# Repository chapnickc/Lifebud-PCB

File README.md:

# Lifebud-PCB

This project contains the schematic 
and board files for the Lifebud project.

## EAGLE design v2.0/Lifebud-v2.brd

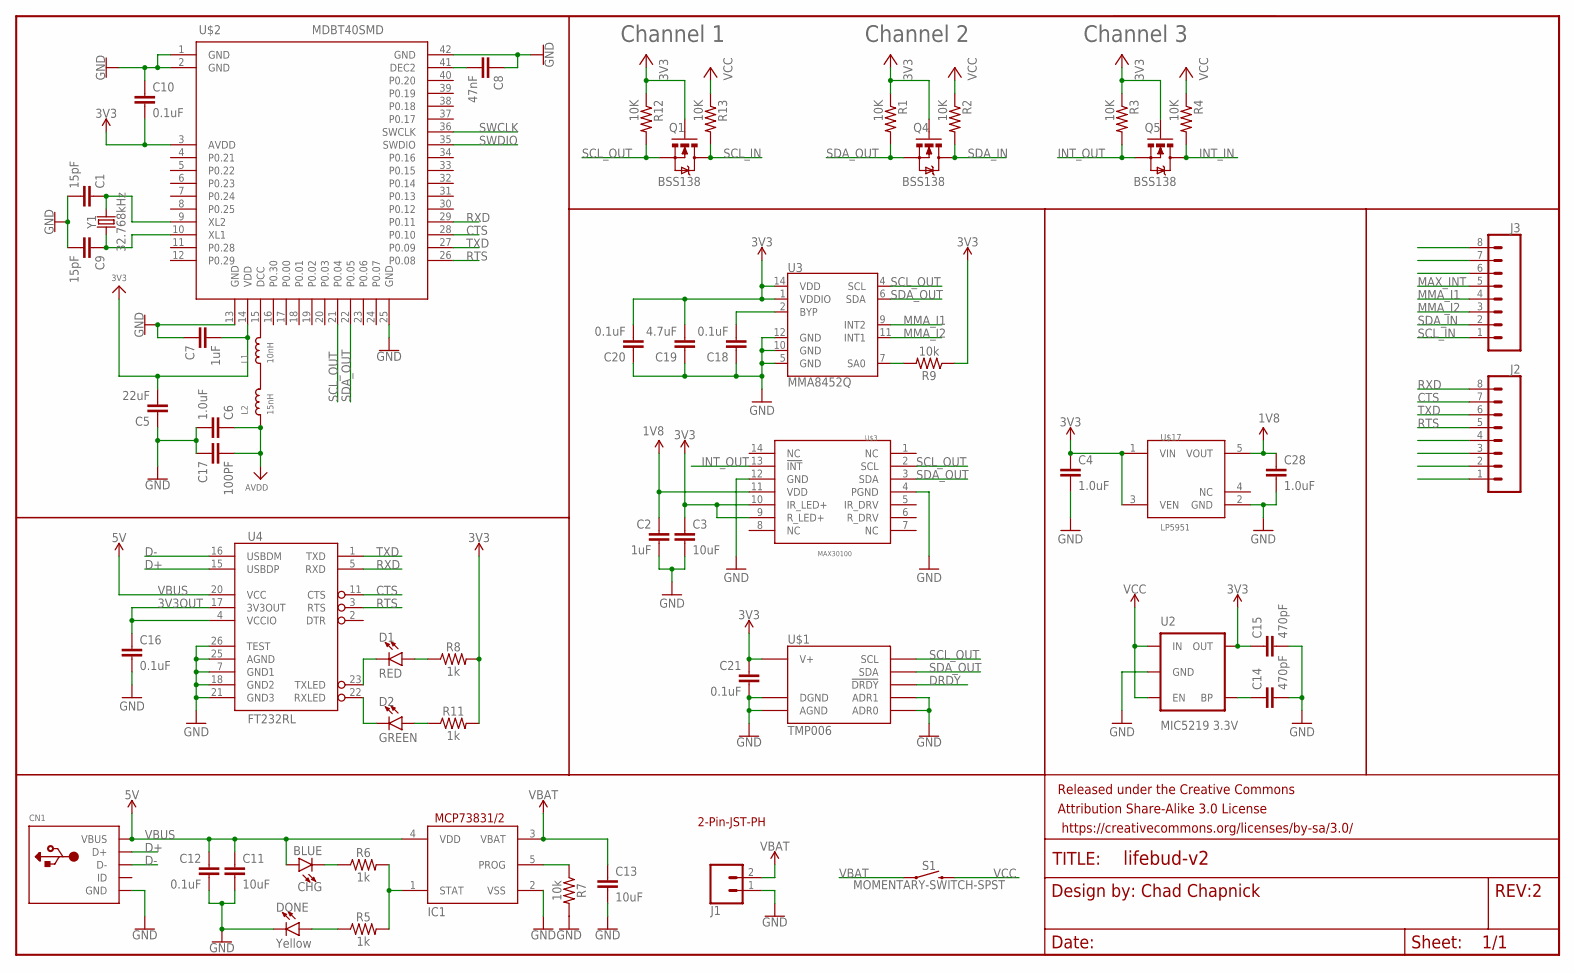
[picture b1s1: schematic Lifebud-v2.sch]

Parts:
C1, C9: 15pF; 0402
C2: 1uF; C0805
C3: 10uF; C0805
C4, C28: 1.0uF; 0402
C5: 22uF; 0805
C6: 1.0uF; 0603
C7: 1uF; 0603
C8: 47nF; 0603
C10, C12, C16, C18, C20, C21: 0.1uF; 0402
C11, C13: 10uF; 0603
C14, C15: 470pF; 0603
C17: 100PF; 0402
C19: 4.7uF; 0603
CHG: BLUE; LED-0603
CN1: USBMINIB; USB-MINIB
D1: RED; LED-0603
D2: GREEN; LED-0603
DONE: Yellow; LED-0603
FRAME1: FRAME-LETTER; CREATIVE_COMMONS
IC1: MCP73831/OT; SOT23-5L
J1: CONN_02-JST-2MM-SMT; JST-2-SMD
J2, J3: CONN_08"; 1X08
L1: 10nH; 0603
L2: 15nH; 0603
Q1, Q4, Q5: BSS138; SOT23-3
R1, R2, R3, R4, R12, R13: 10K; 0402-RES
R5, R6, R8, R11: 1k; 0603
R7, R9: 10k; 0603
S1: MOMENTARY-SWITCH-SPST; TACTILE_SWITCH_SMD_4.6X2.8MM
U2: MIC5219 3.3V; SOT23-5
U3: MMA8452Q; QFN-16
U4: FT232RL; SSOP28DB
U$1: TMP006; BGA8DS
U$2: MDBT40SMD; MDBT40
U$3: MAX30100; OESIP-14
U$17: LP5951; SC70-5
Y1: 32.768kHz; CRYSTAL-SMD-3.2X1.5MM

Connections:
1V8: C2.1, C28.1, U$3.11 (VDD), U$17.5 (VOUT)
3V3: C3.1, C4.1, C5.2, C7.2, C10.2, C15.1, Q1.1 (G), Q4.1 (G), Q5.1 (G), R1.1, R3.1, R8.2, R11.2, R12.1, U2.5 (OUT), U$2.3 (AVDD), U$2.14 (VDD), U$3.9 (R_LED+), U$3.10 (IR_LED+), U$17.1 (VIN), U$17.3 (VEN)
3V3OUT: C16.1, U4.4 (VCCIO), U4.17 (3V3OUT)
AVDD: C6.1, C17.2, L2.1
CTS: J2.7, U4.11 (CTS), U$2.28 (P0.10)
D+: CN1.D+, U4.15 (USBDP)
D-: CN1.D-, U4.16 (USBDM)
DRDY: U$1.C2 (!DRDY)
GND: C1.2, C2.2, C3.2, C4.2, C5.1, C6.2, C7.1, C8.1, C9.2, C10.1, C11.2, C12.2, C13.2, C14.2, C15.2, C16.2, C17.1, C18.1, C19.1, C20.1, C21.2, C28.2, CN1.GND, DONE.C, IC1.2 (VSS), J1.1 (2), R7.2, U2.2 (GND), U3.5 (GND), U3.10 (GND), U3.12 (GND), U4.7 (GND1), U4.18 (GND2), U4.21 (GND3), U4.25 (AGND), U4.26 (TEST), U$1.A1 (DGND), U$1.A2 (AGND), U$1.B1 (ADR1), U$1.C1 (ADR0), U$2.1 (GND), U$2.2 (GND), U$2.13 (GND), U$2.25 (GND), U$2.42 (GND), U$3.4 (PGND), U$3.12 (GND), U$17.2 (GND)
INT_IN: Q5.3 (D), R4.2
INT_OUT: Q5.2 (S), R3.2, U$3.13 (!INT)
MAX_INT: J3.5
MMA_I1: J3.4, U3.9 (INT2)
MMA_I2: J3.3, U3.11 (INT1)
unnamed: C8.2, U$2.41 (DEC2)
unnamed: C9.1, U$2.10 (XL1), Y1.P$1 (1)
unnamed: C1.1, U$2.9 (XL2), Y1.P$2 (2)
unnamed: IC1.1 (STAT), R5.2, R6.2
unnamed: DONE.A, R5.1
unnamed: CHG.C, R6.1
unnamed: IC1.5 (PROG), R7.1
unnamed: C14.1, U2.4 (BP)
unnamed: D1.A, R8.1
unnamed: D2.A, R11.1
unnamed: D1.C, U4.23 (TXLED)
unnamed: D2.C, U4.22 (RXLED)
unnamed: L1.1, L2.2
unnamed: L1.2, U$2.15 (DCC)
unnamed: C18.2, U3.2 (BYP)
unnamed: R9.2, U3.7 (SA0)
RTS: J2.5, U4.3 (RTS), U$2.26 (P0.08)
RXD: J2.8, U4.5 (RXD), U$2.29 (P0.11)
SCL_IN: J3.1, Q1.3 (D), R13.2
SCL_OUT: Q1.2 (S), R12.2, U3.4 (SCL), U$1.B3 (SCL), U$2.21 (P0.04), U$3.2 (SCL)
SDA_IN: J3.2, Q4.3 (D), R2.2
SDA_OUT: Q4.2 (S), R1.2, U3.6 (SDA), U$1.C3 (SDA), U$2.22 (P0.05), U$3.3 (SDA)
SWCLK: U$2.36 (SWCLK)
SWDIO: U$2.35 (SWDIO)
TXD: J2.6, U4.1 (TXD), U$2.27 (P0.09)
VBAT: C13.1, IC1.3 (VBAT), J1.2 (1), S1.1, S1.2 (1)
VBUS: C11.1, C12.1, CHG.A, CN1.VBUS, IC1.4 (VDD), U4.20 (VCC)
VCC: C19.2, C20.2, C21.1, R2.1, R4.1, R9.1, R13.1, S1.3 (2), S1.4 (2), U2.1 (IN), U2.3 (EN), U3.1 (VDDIO), U3.14 (VDD), U$1.A3 (V+)

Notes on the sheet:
Channel 1
Channel 2
Channel 3
2-Pin-JST-PH

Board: 2 copper layers, 58 parts (0 on the bottom side), 38 nets, no tracks yet.

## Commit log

2017-01-20 nearly finished with the DC/DC converter setup on nrf51
2017-01-20 cleaned up schematic, need to check for errors with ERC
2017-01-20 organized components using the line tool

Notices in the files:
parts and their libraries:
SparkFun-Capacitors: Licensing: Creative Commons ShareAlike 4.0 International - https://creativecommons.org/licenses/by-sa/4.0
SparkFun-Retired: Released under the Creative Commons Attribution Share-Alike 3.0 License
SparkFun-Retired: https://creativecommons.org/licenses/by-sa/3.0
